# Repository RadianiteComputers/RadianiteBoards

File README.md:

# Collection of Radianite boards
This is a repository to showcase all of our work onto making Radianite boards. All here are open and licensed under CC-BY-SA-4.0

# Contributing
You will need:
- KiCad 8.0+ (7.0 is okay, but don't install 6.0, 8.0 doesn't support legacy zone filling strategy)
- Git
## Steps
1. Fork and clone this repository into your account
```
https://github.com/<username>/RadianiteBoards/
```
2. Open the `.kicad_pro` file on either project you want to help in.
3. Edit, edit, edit!
4. Commit with your changes. Make sure your commit messages are concise!
5. Finally, create a pull request. A member will look after your design. There are criterias taken into account:
   - Legibility and form factor
   - Trace lengths and signal integrity (advanced computers only like Project Lemon Irvine)
   - Overall impedance (including RF)
   - Possibility for EMI or crosstalks (<1% to be accepted, almost no EMI or crosstalks)
  
# Help with new board ideas
We don't just take our own ideas; in fact: we allow other people to get into Radianite and contribute to new board ideas. Make sure you:
  - have the necessary knowledge on that SoC/MCU
  - think it might be compatible
  - are ready to write some software for that board
  - get creative and have fun!

You don't need to say in words about the ideas; in fact: you can even design that circuit board first as a draft and let our team pick which one to get into Radianite! Make sure you:
  - maximize rounded corners (a radius of 3mm is ideal)
  - make the board aesthetically pleasing as possible
  - add fun elements like sentences, etc
After that, you might earn a shoutout in our mass-produced units.

We hope this revolutionizes how we, as engineers, delivers ideas and fixes in a very open manner. Thank you for choosing Radianite!
© 2024 Radianite Computers. All rights reserved.

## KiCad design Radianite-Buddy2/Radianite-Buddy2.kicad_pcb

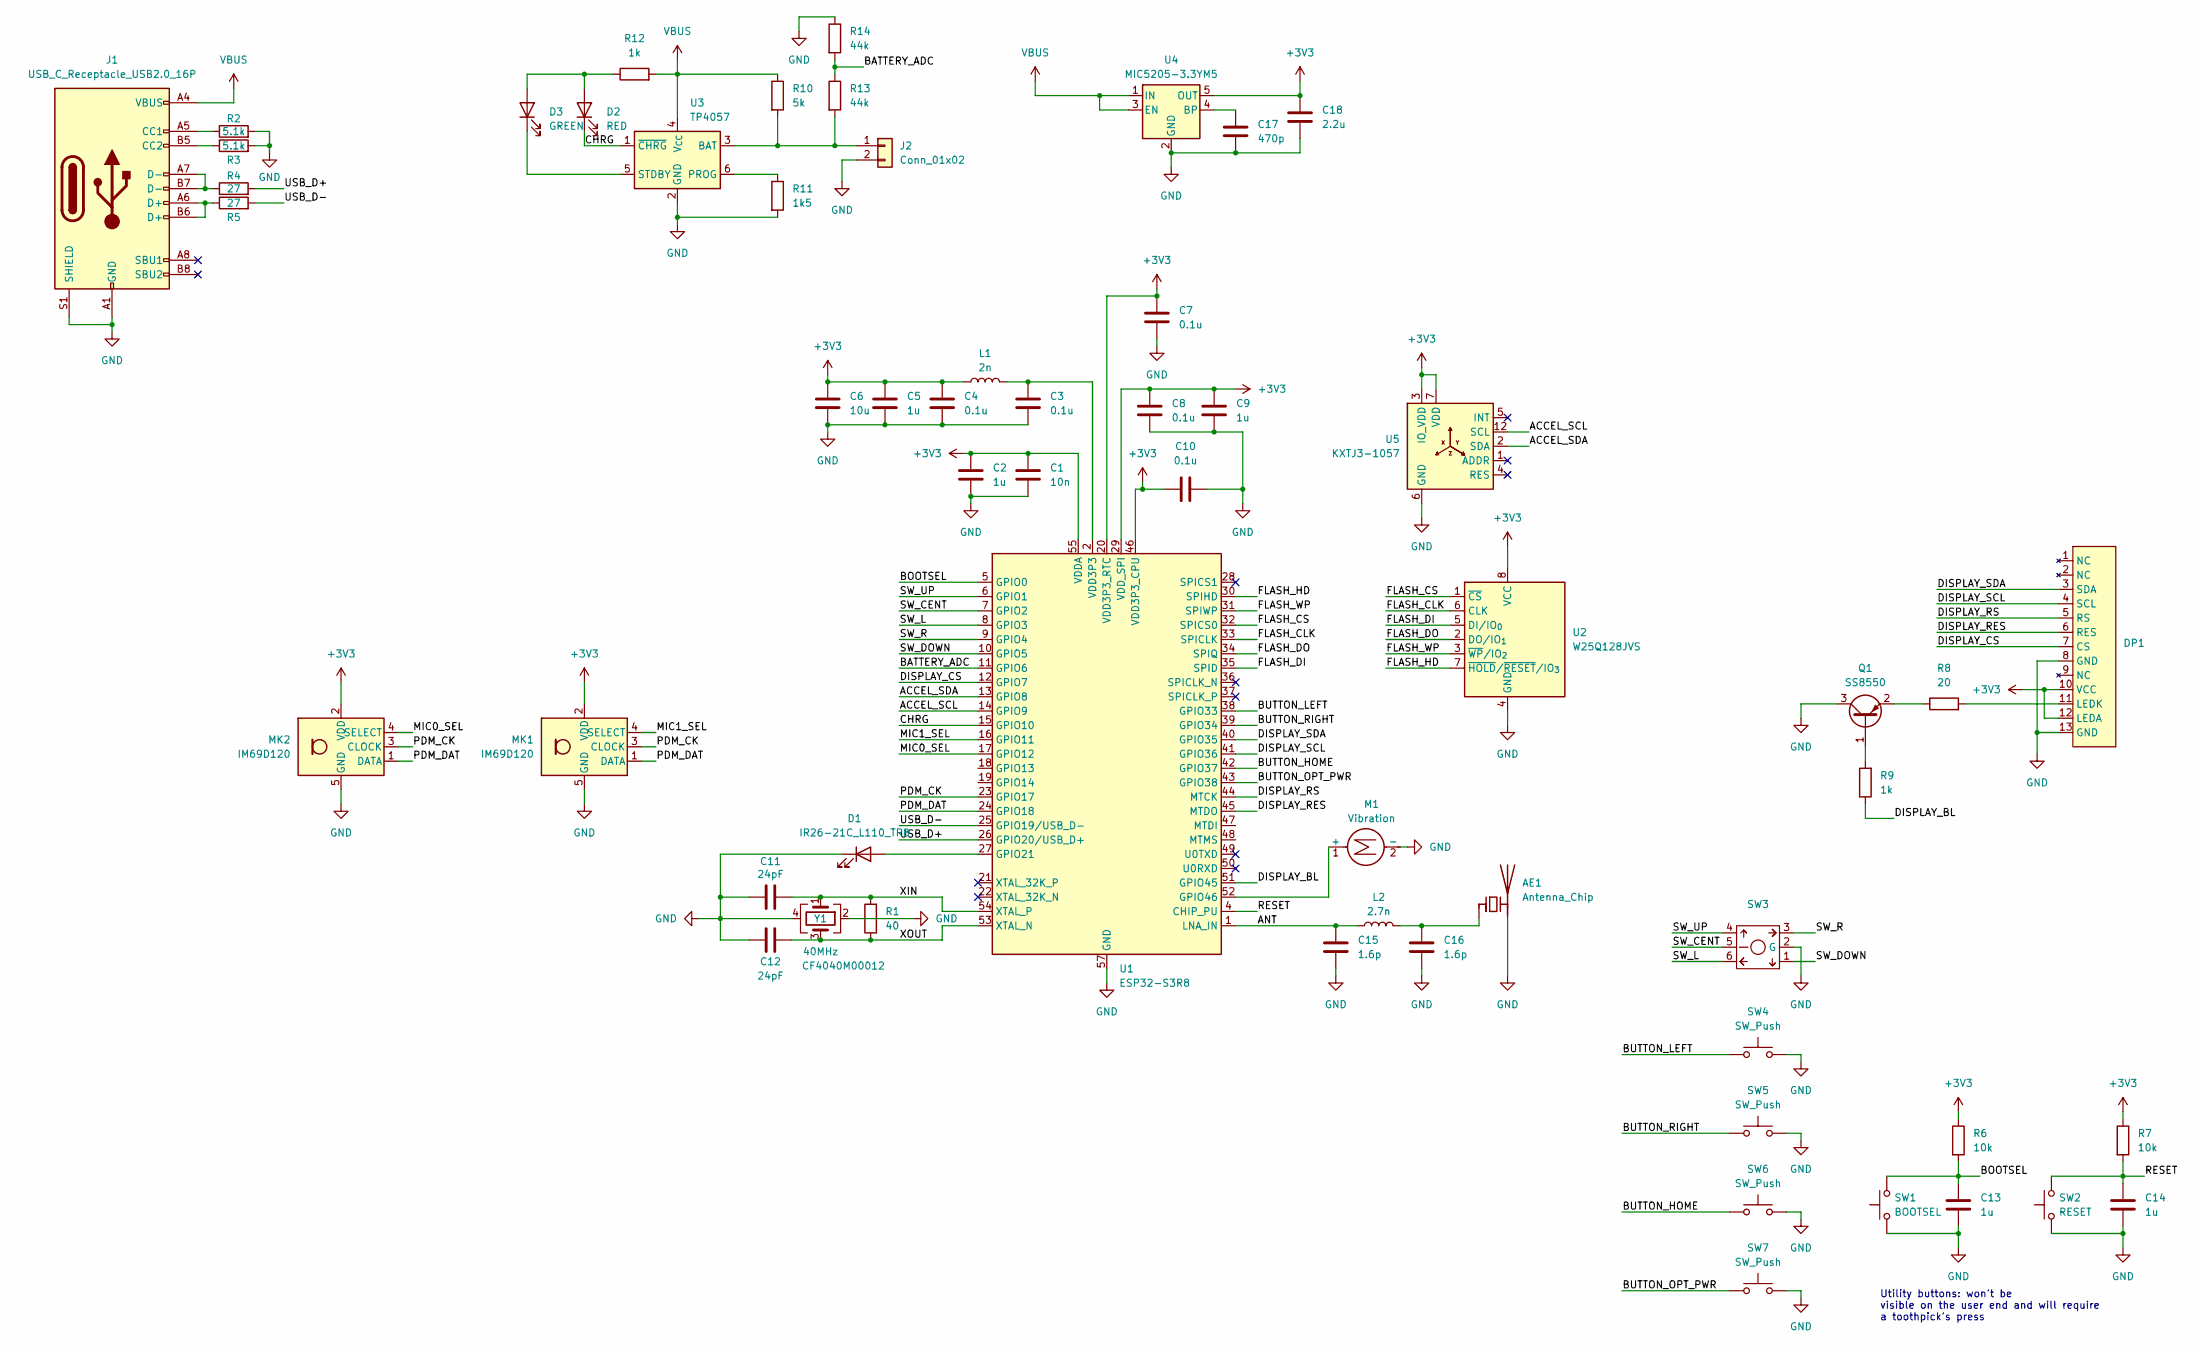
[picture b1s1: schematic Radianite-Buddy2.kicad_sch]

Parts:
AE1: Antenna_Chip; Texas_SWRA117D_2.4GHz_Left
C1: 10n; C_0402_1005Metric
C2, C5, C9, C13, C14: 1u; C_0402_1005Metric
C3, C4, C7, C8, C10: 0.1u; C_0402_1005Metric
C6: 10u; C_0402_1005Metric
C11, C12: 24pF; C_0402_1005Metric
C15, C16: 1.6p; C_0402_1005Metric
C17: 470p; C_0402_1005Metric
C18: 2.2u; C_0402_1005Metric
D1: IR26-21C_L110_TR8; LED_1206_3216Metric
D2: RED; LED_0402_1005Metric
D3: GREEN; LED_0402_1005Metric
DP1: N114-2413THBIG01-H13
J1: USB_C_Receptacle_USB2.0_16P; USB_C_Receptacle_GCT_USB4110
J2: Conn_01x02; JST_PH_S2B-PH-SM4-TB_1x02-1MP_P2.00mm_Horizontal
L1: 2n; L_0402_1005Metric
L2: 2.7n; L_0402_1005Metric
M1: Vibration; Vybronics_VZ30C1T8219732L
MK1, MK2: IM69D120; Infineon_PG-LLGA-5-1
Q1: SS8550; SOT-23
R1: 40; R_0402_1005Metric
R2, R3: 5.1k; R_0402_1005Metric
R4, R5: 27; R_0402_1005Metric
R6, R7: 10k; R_0402_1005Metric
R8: 20; R_0402_1005Metric
R9, R12: 1k; R_0402_1005Metric
R10: 5k; R_0402_1005Metric
R11: 1k5; R_0402_1005Metric
R13, R14: 44k; R_0402_1005Metric
SW1: BOOTSEL; SW_Push_1P1T_NO_CK_KMR2
SW2: RESET; SW_Push_1P1T_NO_CK_KMR2
SW3: SW_Shouhan_MultiDirectional
SW4, SW5, SW6, SW7: SW_Push; SW_Push_1P1T_NO_Vertical_Wuerth_434133025816
U1: ESP32-S3R8; QFN-56-1EP_7x7mm_P0.4mm_EP4x4mm
U2: W25Q128JVS; Winbond_USON-8-1EP_3x2mm_P0.5mm_EP0.2x1.6mm
U3: TP4057; TSOT-23-6
U4: MIC5205-3.3YM5; SOT-23-5
U5: KXTJ3-1057; Kionix_LGA-12_2x2mm_P0.5mm_LayoutBorder2x4y
Y1: 40MHz; Crystal_SMD_3225-4Pin_3.2x2.5mm

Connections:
+3V3: C1.1, C2.1, C4.1, C5.1, C6.1, C7.1, C8.1, C9.1, C10.1, C18.1, DP1.10 (VCC), DP1.12 (LEDA), L1.1, MK1.2 (VDD), MK2.2 (VDD), R6.1, R7.1, U1.20 (VDD3P3_RTC), U1.29 (VDD_SPI), U1.46 (VDD3P3_CPU), U1.55 (VDDA), U1.56 (VDDA), U2.8 (VCC), U4.5 (OUT), U5.3 (IO_VDD), U5.7 (VDD), U5.10 (VDD), U5.11 (IO_VDD)
/ACCEL_SCL: U1.14 (GPIO9), U5.12 (SCL)
/ACCEL_SDA: U1.13 (GPIO8), U5.2 (SDA)
/ANT: C15.1, L2.1, U1.1 (LNA_IN)
/BATTERY_ADC: R13.1, R14.2, U1.11 (GPIO6)
/BOOTSEL: C13.1, R6.2, SW1.2, U1.5 (GPIO0)
/BUTTON_HOME: SW6.1, U1.42 (GPIO37)
/BUTTON_LEFT: SW4.1, U1.38 (GPIO33)
/BUTTON_OPT_PWR: SW7.1, U1.43 (GPIO38)
/BUTTON_RIGHT: SW5.1, U1.39 (GPIO34)
/CHRG: D2.1 (K), U1.15 (GPIO10), U3.1 (~CHRG)
/DISPLAY_BL: R9.1, U1.51 (GPIO45)
/DISPLAY_CS: DP1.7 (CS), U1.12 (GPIO7)
/DISPLAY_RES: DP1.6 (RES), U1.45 (MTDO)
/DISPLAY_RS: DP1.5 (RS), U1.44 (MTCK)
/DISPLAY_SCL: DP1.4 (SCL), U1.41 (GPIO36)
/DISPLAY_SDA: DP1.3 (SDA), U1.40 (GPIO35)
/FLASH_CLK: U1.33 (SPICLK), U2.6 (CLK)
/FLASH_CS: U1.32 (SPICS0), U2.1 (~CS)
/FLASH_DI: U1.35 (SPID), U2.5 (DI/IO_{0})
/FLASH_DO: U1.34 (SPIQ), U2.2 (DO/IO_{1})
/FLASH_HD: U1.30 (SPIHD), U2.7 (~HOLD/~RESET/IO_{3})
/FLASH_WP: U1.31 (SPIWP), U2.3 (~WP/IO_{2})
/MIC0_SEL: MK2.4 (SELECT), U1.17 (GPIO12)
/MIC1_SEL: MK1.4 (SELECT), U1.16 (GPIO11)
/PDM_CK: MK1.3 (CLOCK), MK2.3 (CLOCK), U1.23 (GPIO17)
/PDM_DAT: MK1.1 (DATA), MK2.1 (DATA), U1.24 (GPIO18)
/RESET: C14.1, R7.2, SW2.2, U1.4 (CHIP_PU)
/SW_CENT: SW3.5, U1.7 (GPIO2)
/SW_DOWN: SW3.1, U1.10 (GPIO5)
/SW_L: SW3.6, U1.8 (GPIO3)
/SW_R: SW3.3, U1.9 (GPIO4)
/SW_UP: SW3.4, U1.6 (GPIO1)
/USB_D+: R4.2, U1.26 (GPIO20/USB_D+)
/USB_D-: R5.2, U1.25 (GPIO19/USB_D-)
/XIN: C11.1, R1.2, U1.54 (XTAL_P), Y1.1
/XOUT: C12.1, R1.1, U1.53 (XTAL_N), Y1.3
GND: AE1.2 (PCB_Trace), C1.2, C2.2, C3.2, C4.2, C5.2, C6.2, C7.2, C8.2, C9.2, C10.2, C11.2, C12.2, C13.2, C14.2, C15.2, C16.2, C17.2, C18.2, D1.1 (K), DP1.8 (GND), DP1.13 (GND), J1.A1 (GND), J1.A12 (GND), J1.B1 (GND), J1.B12 (GND), J1.S1 (SHIELD), J2.2, M1.2 (-), MK1.5 (GND), MK2.5 (GND), Q1.3 (C), R2.2, R3.2, R11.2, R14.1, SW1.1, SW2.1, SW3.2 (G), SW4.2, SW5.2, SW6.2, SW7.2, U1.57 (GND), U2.4 (GND), U3.2 (GND), U4.2 (GND), U5.6 (GND), U5.8 (GND), U5.9 (GND), Y1.2, Y1.4
unnamed: AE1.1 (FEED), C16.1, L2.2
unnamed: C3.1, L1.2, U1.2 (VDD3P3), U1.3 (VDD3P3)
unnamed: D1.2 (A), U1.27 (GPIO21)
unnamed: D2.2 (A), D3.2 (A), R12.1
unnamed: D3.1 (K), U3.5 (STDBY)
unnamed: DP1.11 (LEDK), R8.2
unnamed: J1.A5 (CC1), R2.1
unnamed: J1.B5 (CC2), R3.1
unnamed: J1.A6 (D+), J1.B6 (D+), R5.1
unnamed: J1.A7 (D-), J1.B7 (D-), R4.1
unnamed: J2.1, R10.2, R13.2, U3.3 (BAT)
unnamed: M1.1 (+), U1.52 (GPIO46)
unnamed: Q1.1 (B), R9.2
unnamed: Q1.2 (E), R8.1
unnamed: R11.1, U3.6 (PROG)
unnamed: C17.1, U4.4 (BP)
VBUS: J1.A4 (VBUS), J1.A9 (VBUS), J1.B4 (VBUS), J1.B9 (VBUS), R10.1, R12.2, U3.4 (V_{CC}), U4.1 (IN), U4.3 (EN)

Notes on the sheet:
Utility buttons: won't be visible on the user end and will require a toothpick's press

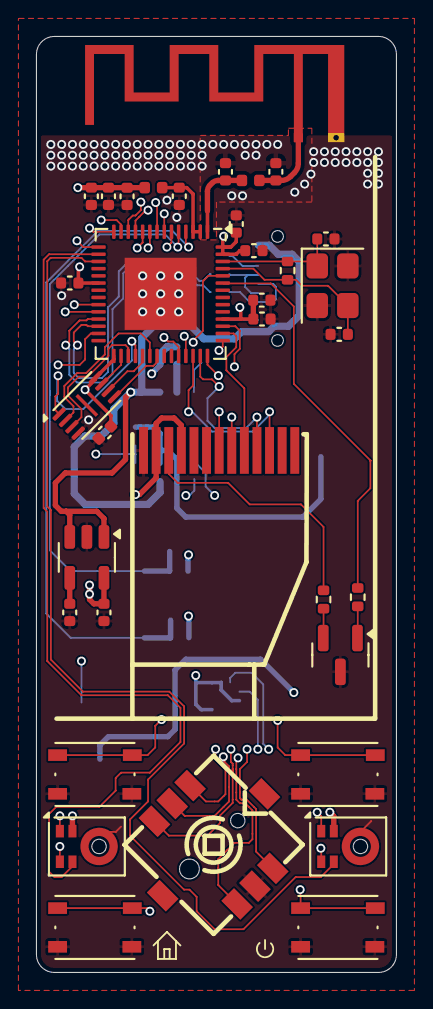
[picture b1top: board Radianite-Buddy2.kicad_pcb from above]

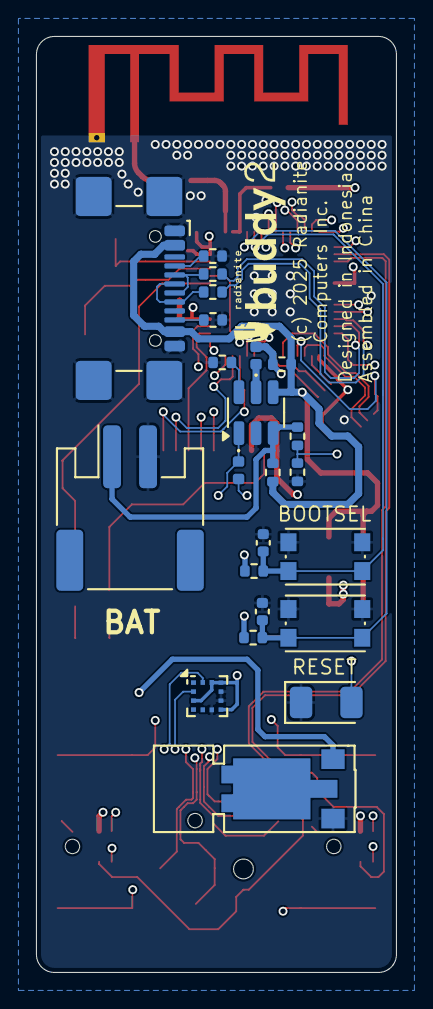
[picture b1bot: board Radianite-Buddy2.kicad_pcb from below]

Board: 4 copper layers, 20.0 x 52.0 mm, 58 parts (23 on the bottom side), 55 nets.

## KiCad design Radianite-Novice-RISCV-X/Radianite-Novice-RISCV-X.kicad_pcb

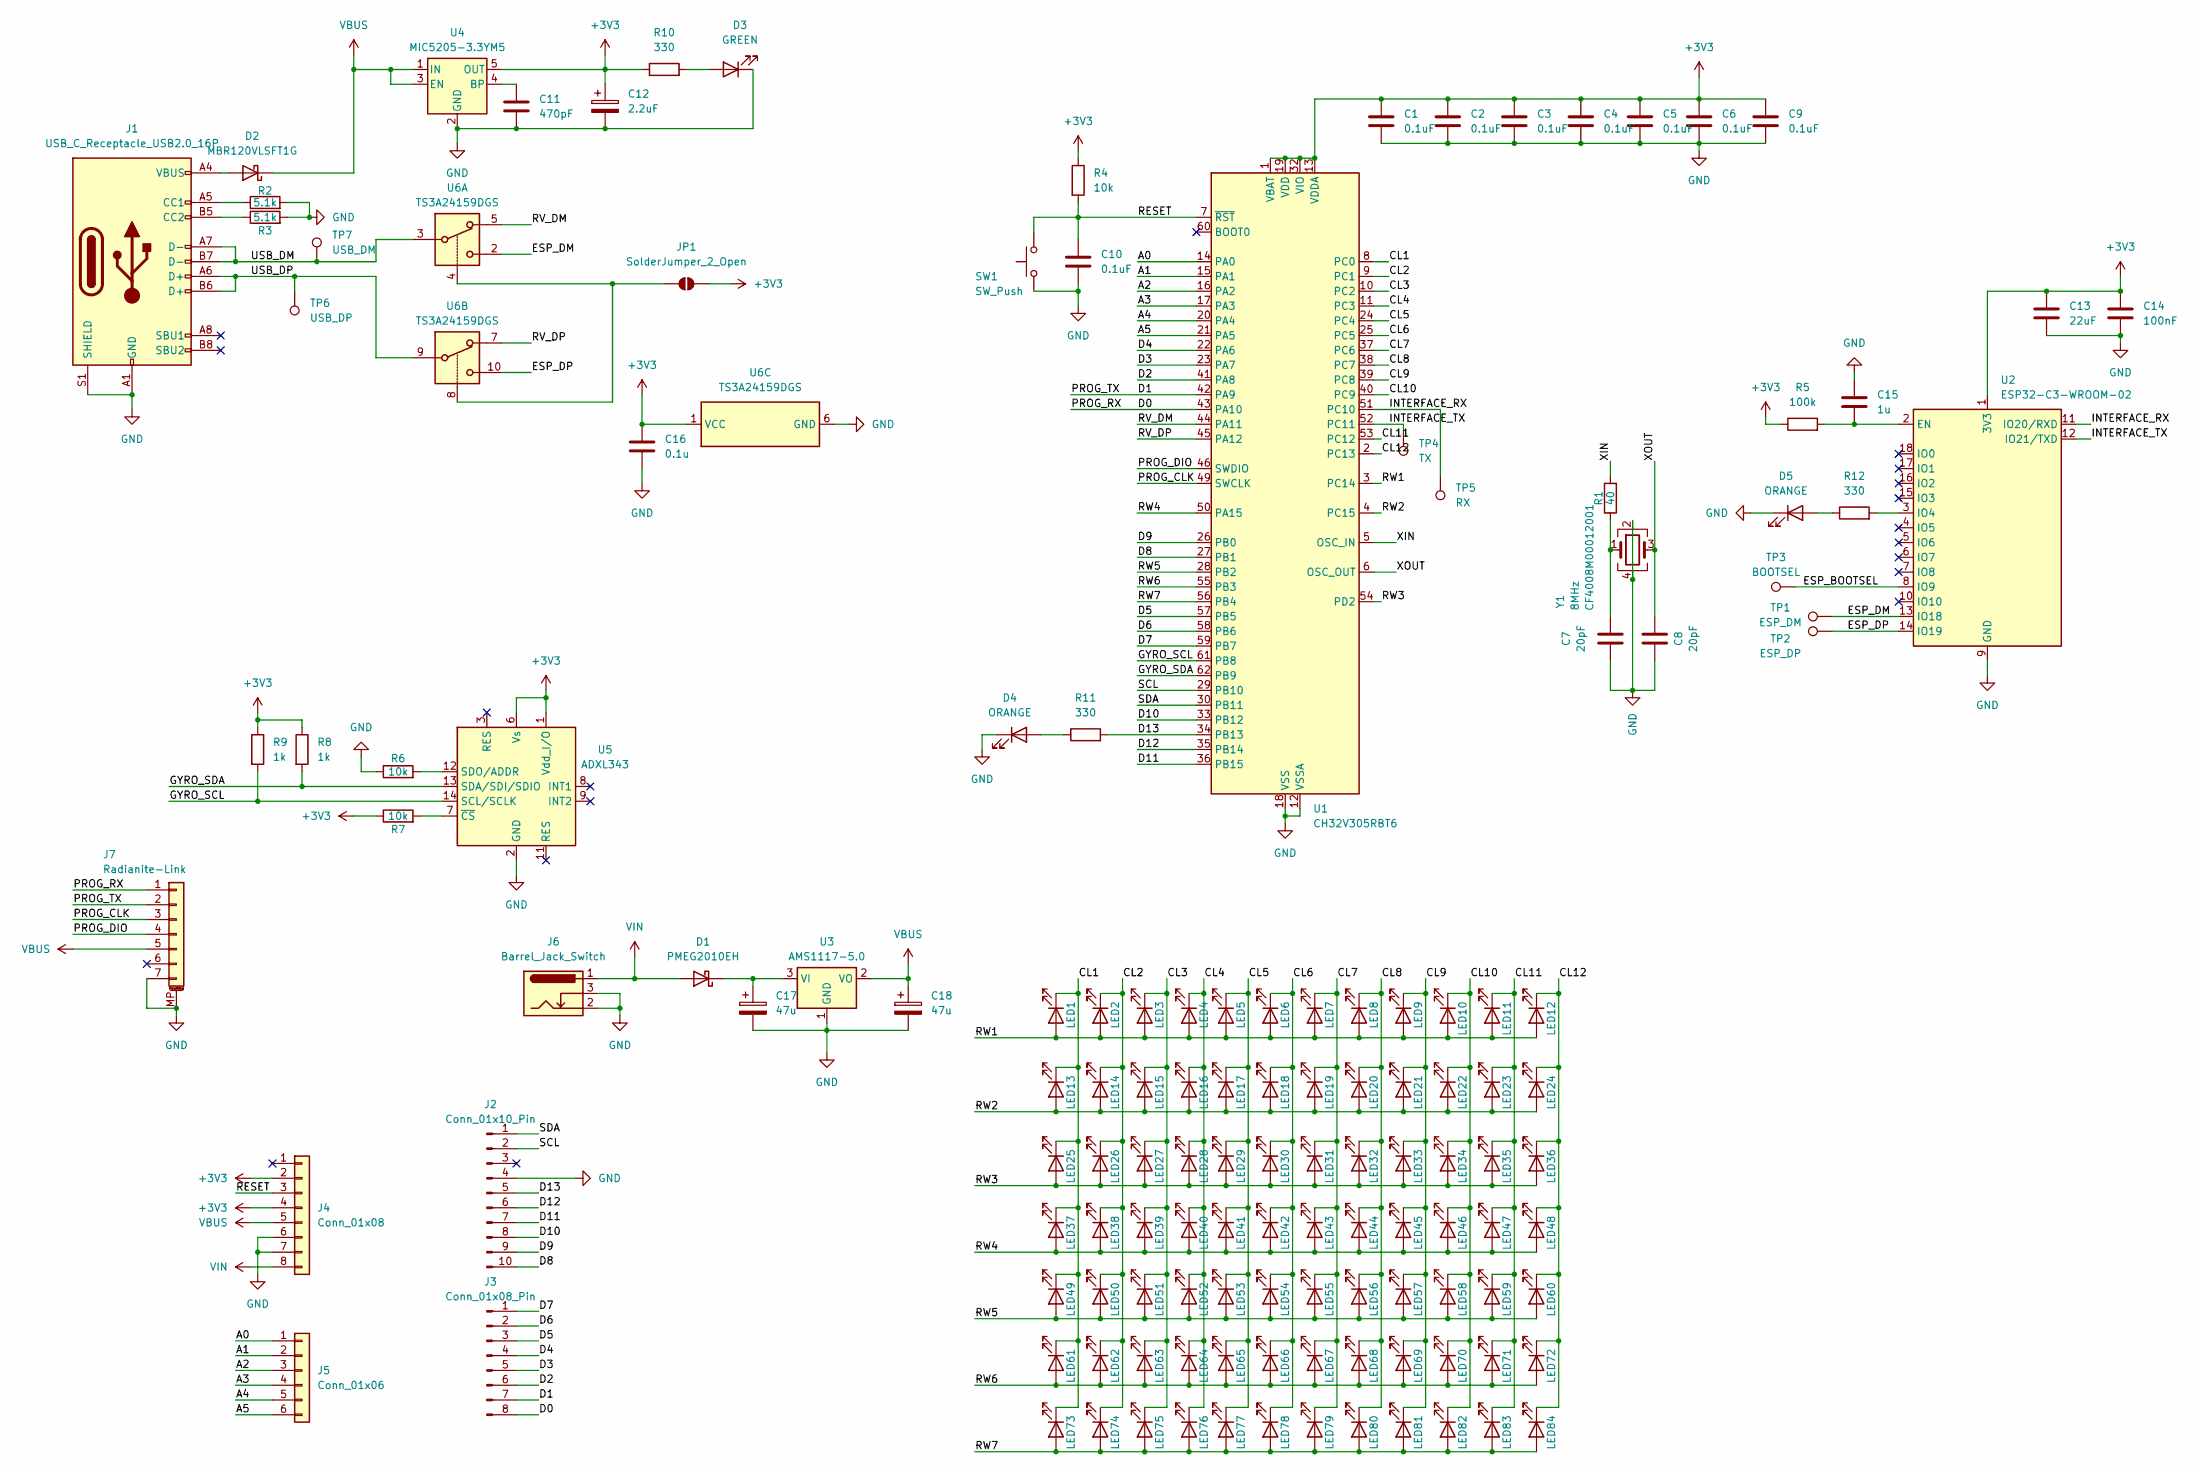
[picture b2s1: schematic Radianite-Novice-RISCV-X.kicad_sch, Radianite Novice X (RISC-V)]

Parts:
C1, C2, C3, C4, C5, C6, C9, C10: 0.1uF; C_0402_1005Metric
C7, C8: 20pF; C_0402_1005Metric
C11: 470pF; C_0402_1005Metric
C12: 2.2uF; CP_EIA-1608-08_AVX-J
C13: 22uF; C_0402_1005Metric
C14: 100nF; C_0402_1005Metric
C15: 1u; C_0402_1005Metric
C16: 0.1u; C_0603_1608Metric
C17, C18: 47u; CP_Elec_3x5.3
D1: PMEG2010EH; D_SOD-123F
D2: MBR120VLSFT1G; D_SOD-123F
D3: GREEN; LED_0402_1005Metric
D4, D5: ORANGE; LED_0402_1005Metric
J1: USB_C_Receptacle_USB2.0_16P; USB_C_Receptacle_GCT_USB4105-xx-A_16P_TopMnt_Horizontal
J2: Conn_01x10_Pin; PinSocket_1x10_P2.54mm_Vertical
J3: Conn_01x08_Pin; PinSocket_1x08_P2.54mm_Vertical
J4: Conn_01x08; PinSocket_1x08_P2.54mm_Vertical
J5: Conn_01x06; PinSocket_1x06_P2.54mm_Vertical
J6: Barrel_Jack_Switch; BarrelJack_Horizontal
J7: Radianite-Link; JST_SH_SM07B-SRSS-TB_1x07-1MP_P1.00mm_Horizontal
JP1: SolderJumper_2_Open; SolderJumper-2_P1.3mm_Open_RoundedPad1.0x1.5mm
LED1, LED2, LED3, LED4, LED5, LED6, LED7, LED8, LED9, LED10, LED11, LED12, LED13, LED14, LED15, LED16, LED17, LED18, LED19, LED20, LED21, LED22, LED23, LED24, LED25, LED26, LED27, LED28, LED29, LED30, LED31, LED32, LED33, LED34, LED35, LED36, LED37, LED38, LED39, LED40, LED41, LED42, LED43, LED44, LED45, LED46, LED47, LED48, LED49, LED50, LED51, LED52, LED53, LED54, LED55, LED56, LED57, LED58, LED59, LED60, LED61, LED62, LED63, LED64, LED65, LED66, LED67, LED68, LED69, LED70, LED71, LED72, LED73, LED74, LED75, LED76, LED77, LED78, LED79, LED80, LED81, LED82, LED83, LED84: LED; LED_0402_1005Metric
R1: 40; R_0402_1005Metric
R2, R3: 5.1k; R_0402_1005Metric
R4, R6, R7: 10k; R_0402_1005Metric
R5: 100k; R_0402_1005Metric
R8, R9: 1k; R_0402_1005Metric
R10, R11, R12: 330; R_0402_1005Metric
SW1: SW_Push; SW_SPST_Omron_B3FS-100xP
TP1: ESP_DM; TestPoint_Pad_D1.0mm
TP2: ESP_DP; TestPoint_Pad_D1.0mm
TP3: BOOTSEL; TestPoint_Pad_D1.0mm
TP4: TX; TestPoint_Pad_D1.0mm
TP5: RX; TestPoint_Pad_D1.0mm
TP6: USB_DP; TestPoint_Pad_D1.0mm
TP7: USB_DM; TestPoint_Pad_D1.0mm
U1: CH32V305RBT6; LQFP-64_10x10mm_P0.5mm
U2: ESP32-C3-WROOM-02
U3: AMS1117-5.0; SOT-223-3_TabPin2
U4: MIC5205-3.3YM5; SOT-23-5
U5: ADXL343; LGA-14_3x5mm_P0.8mm_LayoutBorder1x6y
U6: TS3A24159DGS; TSSOP-10_3x3mm_P0.5mm
Y1: 8MHz; Crystal_SMD_3225-4Pin_3.2x2.5mm

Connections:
+3V3: C1.1, C2.1, C3.1, C4.1, C5.1, C6.1, C9.1, C12.1, C13.1, C14.1, C16.1, J4.2, J4.4, JP1.2 (B), R4.1, R5.1, R7.1, R8.1, R9.1, R10.1, U1.1 (VBAT), U1.13 (VDDA), U1.19 (VDD), U1.32 (VIO), U1.48 (VDD), U1.64 (VIO), U2.1 (3V3), U4.5 (OUT), U5.1 (Vdd_I/O), U5.6 (Vs), U6.1 (VCC)
/A0: J5.1, U1.14 (PA0)
/A1: J5.2, U1.15 (PA1)
/A2: J5.3, U1.16 (PA2)
/A3: J5.4, U1.17 (PA3)
/A4: J5.5, U1.20 (PA4)
/A5: J5.6, U1.21 (PA5)
/CL1: LED1.1 (K), LED13.1 (K), LED25.1 (K), LED37.1 (K), LED49.1 (K), LED61.1 (K), LED73.1 (K), U1.8 (PC0)
/CL2: LED2.1 (K), LED14.1 (K), LED26.1 (K), LED38.1 (K), LED50.1 (K), LED62.1 (K), LED74.1 (K), U1.9 (PC1)
/CL3: LED3.1 (K), LED15.1 (K), LED27.1 (K), LED39.1 (K), LED51.1 (K), LED63.1 (K), LED75.1 (K), U1.10 (PC2)
/CL4: LED4.1 (K), LED16.1 (K), LED28.1 (K), LED40.1 (K), LED52.1 (K), LED64.1 (K), LED76.1 (K), U1.11 (PC3)
/CL5: LED5.1 (K), LED17.1 (K), LED29.1 (K), LED41.1 (K), LED53.1 (K), LED65.1 (K), LED77.1 (K), U1.24 (PC4)
/CL6: LED6.1 (K), LED18.1 (K), LED30.1 (K), LED42.1 (K), LED54.1 (K), LED66.1 (K), LED78.1 (K), U1.25 (PC5)
/CL7: LED7.1 (K), LED19.1 (K), LED31.1 (K), LED43.1 (K), LED55.1 (K), LED67.1 (K), LED79.1 (K), U1.37 (PC6)
/CL8: LED8.1 (K), LED20.1 (K), LED32.1 (K), LED44.1 (K), LED56.1 (K), LED68.1 (K), LED80.1 (K), U1.38 (PC7)
/CL9: LED9.1 (K), LED21.1 (K), LED33.1 (K), LED45.1 (K), LED57.1 (K), LED69.1 (K), LED81.1 (K), U1.39 (PC8)
/CL10: LED10.1 (K), LED22.1 (K), LED34.1 (K), LED46.1 (K), LED58.1 (K), LED70.1 (K), LED82.1 (K), U1.40 (PC9)
/CL11: LED11.1 (K), LED23.1 (K), LED35.1 (K), LED47.1 (K), LED59.1 (K), LED71.1 (K), LED83.1 (K), U1.53 (PC12)
/CL12: LED12.1 (K), LED24.1 (K), LED36.1 (K), LED48.1 (K), LED60.1 (K), LED72.1 (K), LED84.1 (K), U1.2 (PC13)
/D0: J3.8, J7.1, U1.43 (PA10)
/D1: J3.7, J7.2, U1.42 (PA9)
/D2: J3.6, U1.41 (PA8)
/D3: J3.5, U1.23 (PA7)
/D4: J3.4, U1.22 (PA6)
/D5: J3.3, U1.57 (PB5)
/D6: J3.2, U1.58 (PB6)
/D7: J3.1, U1.59 (PB7)
/D8: J2.10, U1.27 (PB1)
/D9: J2.9, U1.26 (PB0)
/D10: J2.8, U1.33 (PB12)
/D11: J2.7, U1.36 (PB15)
/D12: J2.6, U1.35 (PB14)
/D13: J2.5, R11.2, U1.34 (PB13)
/ESP_BOOTSEL: TP3.1, U2.8 (IO9)
/ESP_DM: TP1.1, U2.13 (IO18), U6.2
/ESP_DP: TP2.1, U2.14 (IO19), U6.10
/GYRO_SCL: R9.2, U1.61 (PB8), U5.14 (SCL/SCLK)
/GYRO_SDA: R8.2, U1.62 (PB9), U5.13 (SDA/SDI/SDIO)
/INTERFACE_RX: TP5.1, U1.51 (PC10), U2.11 (IO20/RXD)
/INTERFACE_TX: TP4.1, U1.52 (PC11), U2.12 (IO21/TXD)
/PROG_CLK: J7.3, U1.49 (SWCLK)
/PROG_DIO: J7.4, U1.46 (SWDIO)
/RESET: C10.1, J4.3, R4.2, SW1.2, U1.7 (~RST)
/RV_DM: U1.44 (PA11), U6.5
/RV_DP: U1.45 (PA12), U6.7
/RW1: LED1.2 (A), LED2.2 (A), LED3.2 (A), LED4.2 (A), LED5.2 (A), LED6.2 (A), LED7.2 (A), LED8.2 (A), LED9.2 (A), LED10.2 (A), LED11.2 (A), LED12.2 (A), U1.3 (PC14)
/RW2: LED13.2 (A), LED14.2 (A), LED15.2 (A), LED16.2 (A), LED17.2 (A), LED18.2 (A), LED19.2 (A), LED20.2 (A), LED21.2 (A), LED22.2 (A), LED23.2 (A), LED24.2 (A), U1.4 (PC15)
/RW3: LED25.2 (A), LED26.2 (A), LED27.2 (A), LED28.2 (A), LED29.2 (A), LED30.2 (A), LED31.2 (A), LED32.2 (A), LED33.2 (A), LED34.2 (A), LED35.2 (A), LED36.2 (A), U1.54 (PD2)
/RW4: LED37.2 (A), LED38.2 (A), LED39.2 (A), LED40.2 (A), LED41.2 (A), LED42.2 (A), LED43.2 (A), LED44.2 (A), LED45.2 (A), LED46.2 (A), LED47.2 (A), LED48.2 (A), U1.50 (PA15)
/RW5: LED49.2 (A), LED50.2 (A), LED51.2 (A), LED52.2 (A), LED53.2 (A), LED54.2 (A), LED55.2 (A), LED56.2 (A), LED57.2 (A), LED58.2 (A), LED59.2 (A), LED60.2 (A), U1.28 (PB2)
/RW6: LED61.2 (A), LED62.2 (A), LED63.2 (A), LED64.2 (A), LED65.2 (A), LED66.2 (A), LED67.2 (A), LED68.2 (A), LED69.2 (A), LED70.2 (A), LED71.2 (A), LED72.2 (A), U1.55 (PB3)
/RW7: LED73.2 (A), LED74.2 (A), LED75.2 (A), LED76.2 (A), LED77.2 (A), LED78.2 (A), LED79.2 (A), LED80.2 (A), LED81.2 (A), LED82.2 (A), LED83.2 (A), LED84.2 (A), U1.56 (PB4)
/SCL: J2.2, U1.29 (PB10)
/SDA: J2.1, U1.30 (PB11)
/USB_DM: J1.A7 (D-), J1.B7 (D-), TP7.1, U6.3
/USB_DP: J1.A6 (D+), J1.B6 (D+), TP6.1, U6.9
/XIN: R1.2, U1.5 (OSC_IN)
/XOUT: C8.1, U1.6 (OSC_OUT), Y1.3
GND: C1.2, C2.2, C3.2, C4.2, C5.2, C6.2, C7.1, C8.2, C9.2, C10.2, C11.2, C12.2, C13.2, C14.2, C15.1, C16.2, C17.2, C18.2, D3.1 (K), D4.1 (K), D5.1 (K), J1.A1 (GND), J1.A12 (GND), J1.B1 (GND), J1.B12 (GND), J1.S1 (SHIELD), J2.4, J4.6, J4.7, J6.2, J6.3, J7.7, J7.MP (MountPin), R2.2, R3.2, R6.1, SW1.1, U1.12 (VSSA), U1.18 (VSS), U1.31 (VSS), U1.47 (VSS), U1.63 (VSS), U2.9 (GND), U2.19 (GND), U3.1 (GND), U4.2 (GND), U5.2 (GND), U5.4 (GND), U5.5 (GND), U6.6 (GND), Y1.2, Y1.4
unnamed: C7.2, R1.1, Y1.1
unnamed: C17.1, D1.1 (K), U3.3 (VI)
unnamed: D2.2 (A), J1.A4 (VBUS), J1.A9 (VBUS), J1.B4 (VBUS), J1.B9 (VBUS)
unnamed: D3.2 (A), R10.2
unnamed: D4.2 (A), R11.1
unnamed: D5.2 (A), R12.1
unnamed: J1.A5 (CC1), R2.1
unnamed: J1.B5 (CC2), R3.1
unnamed: JP1.1 (A), U6.4, U6.8
unnamed: C15.2, R5.2, U2.2 (EN)
unnamed: R12.2, U2.3 (IO4)
unnamed: C11.1, U4.4 (BP)
unnamed: R6.2, U5.12 (SDO/ADDR)
unnamed: R7.2, U5.7 (~CS)
VBUS: C18.1, D2.1 (K), J4.5, J7.5, U3.2 (VO), U4.1 (IN), U4.3 (EN)
VIN: D1.2 (A), J4.8, J6.1

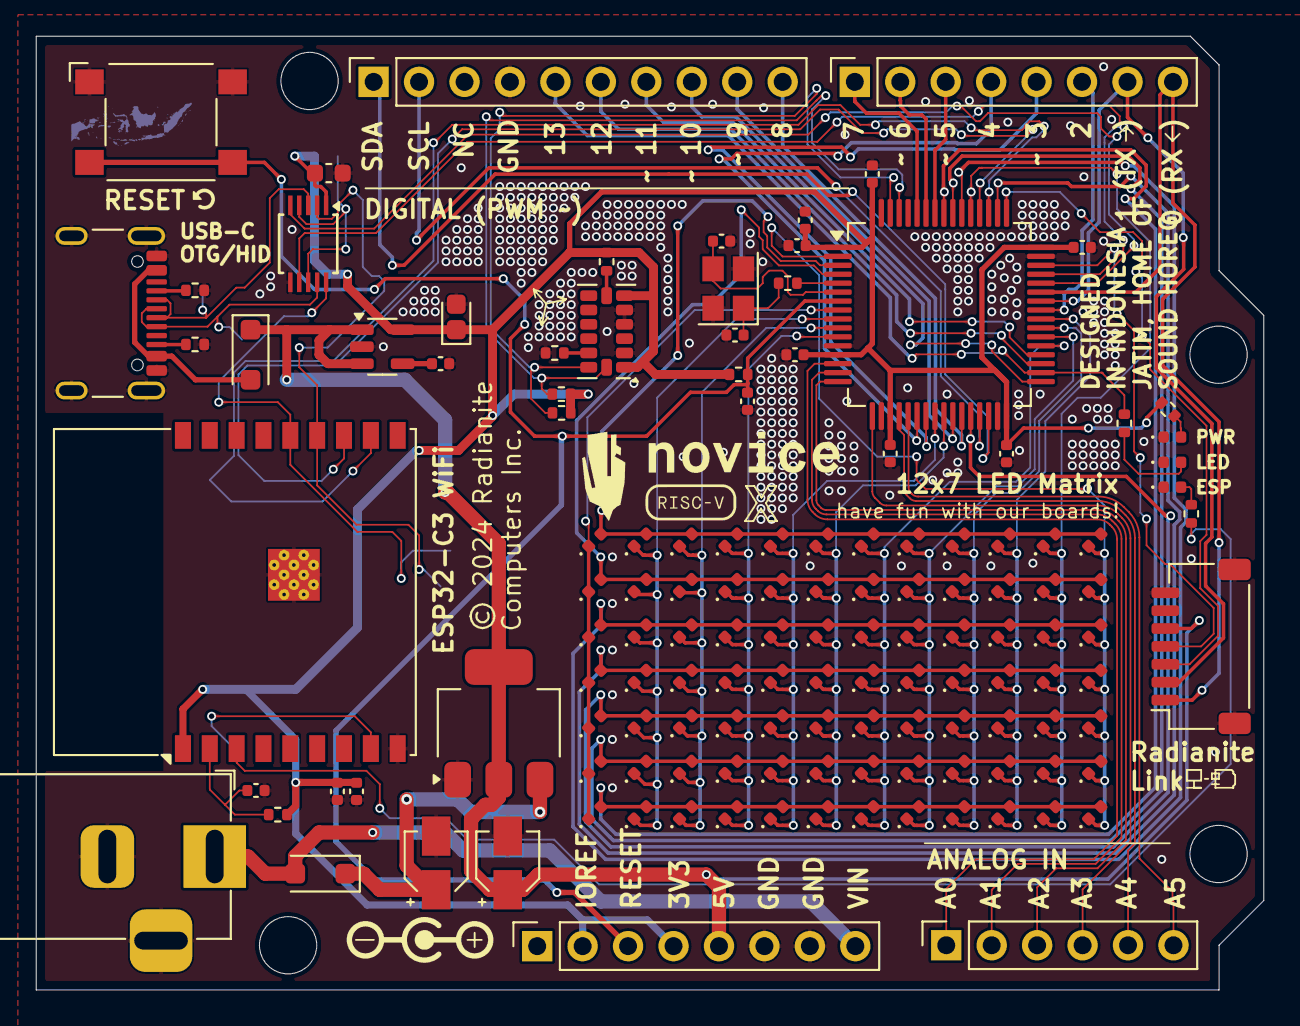
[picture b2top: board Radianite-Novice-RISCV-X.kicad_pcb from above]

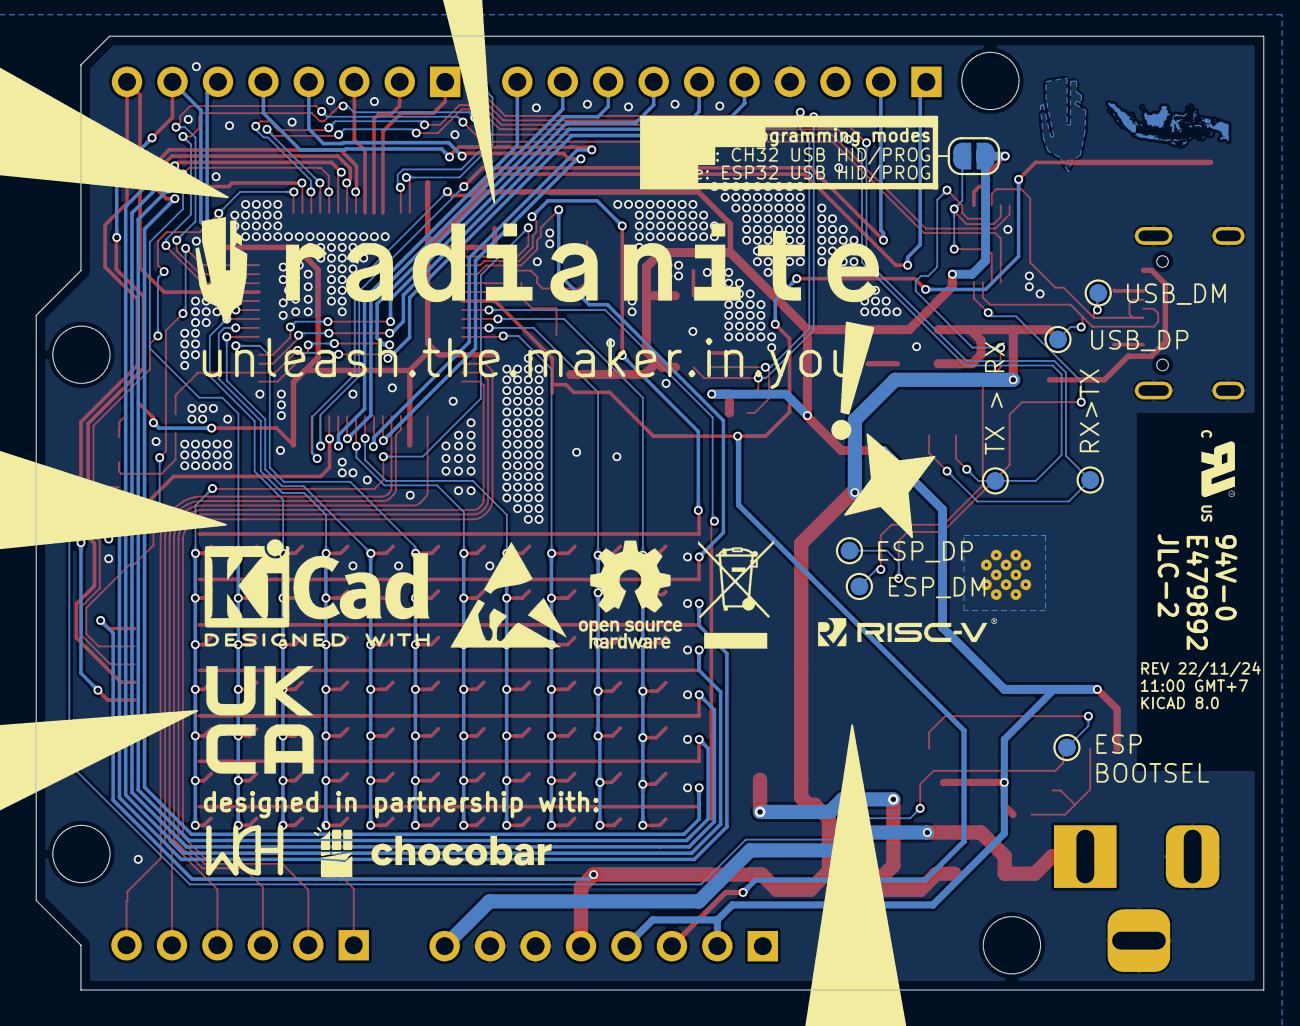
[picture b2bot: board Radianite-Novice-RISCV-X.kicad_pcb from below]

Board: 2 copper layers, 68.6 x 53.3 mm, 146 parts (8 on the bottom side), 75 nets.

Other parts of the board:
MH1, MH2, MH3, MH4: MountingHole_3.2mm_M3

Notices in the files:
Radianite-Buddy2/Radianite-Buddy2.kicad_pcb:
(c) 2025 Radianite
Radianite-MicroNeo2/Radianite-MicroNeo2.kicad_pcb:
© 2025 Radianite Computers
Radianite-uFM/Radianite-uFM.kicad_sch:
(c) 2024 Radianite Computers
